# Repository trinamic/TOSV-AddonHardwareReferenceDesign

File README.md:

# TOSV-AddonHardwareReferenceDesign
Reference Design for the TOSV Pressure Sensor Addon Board

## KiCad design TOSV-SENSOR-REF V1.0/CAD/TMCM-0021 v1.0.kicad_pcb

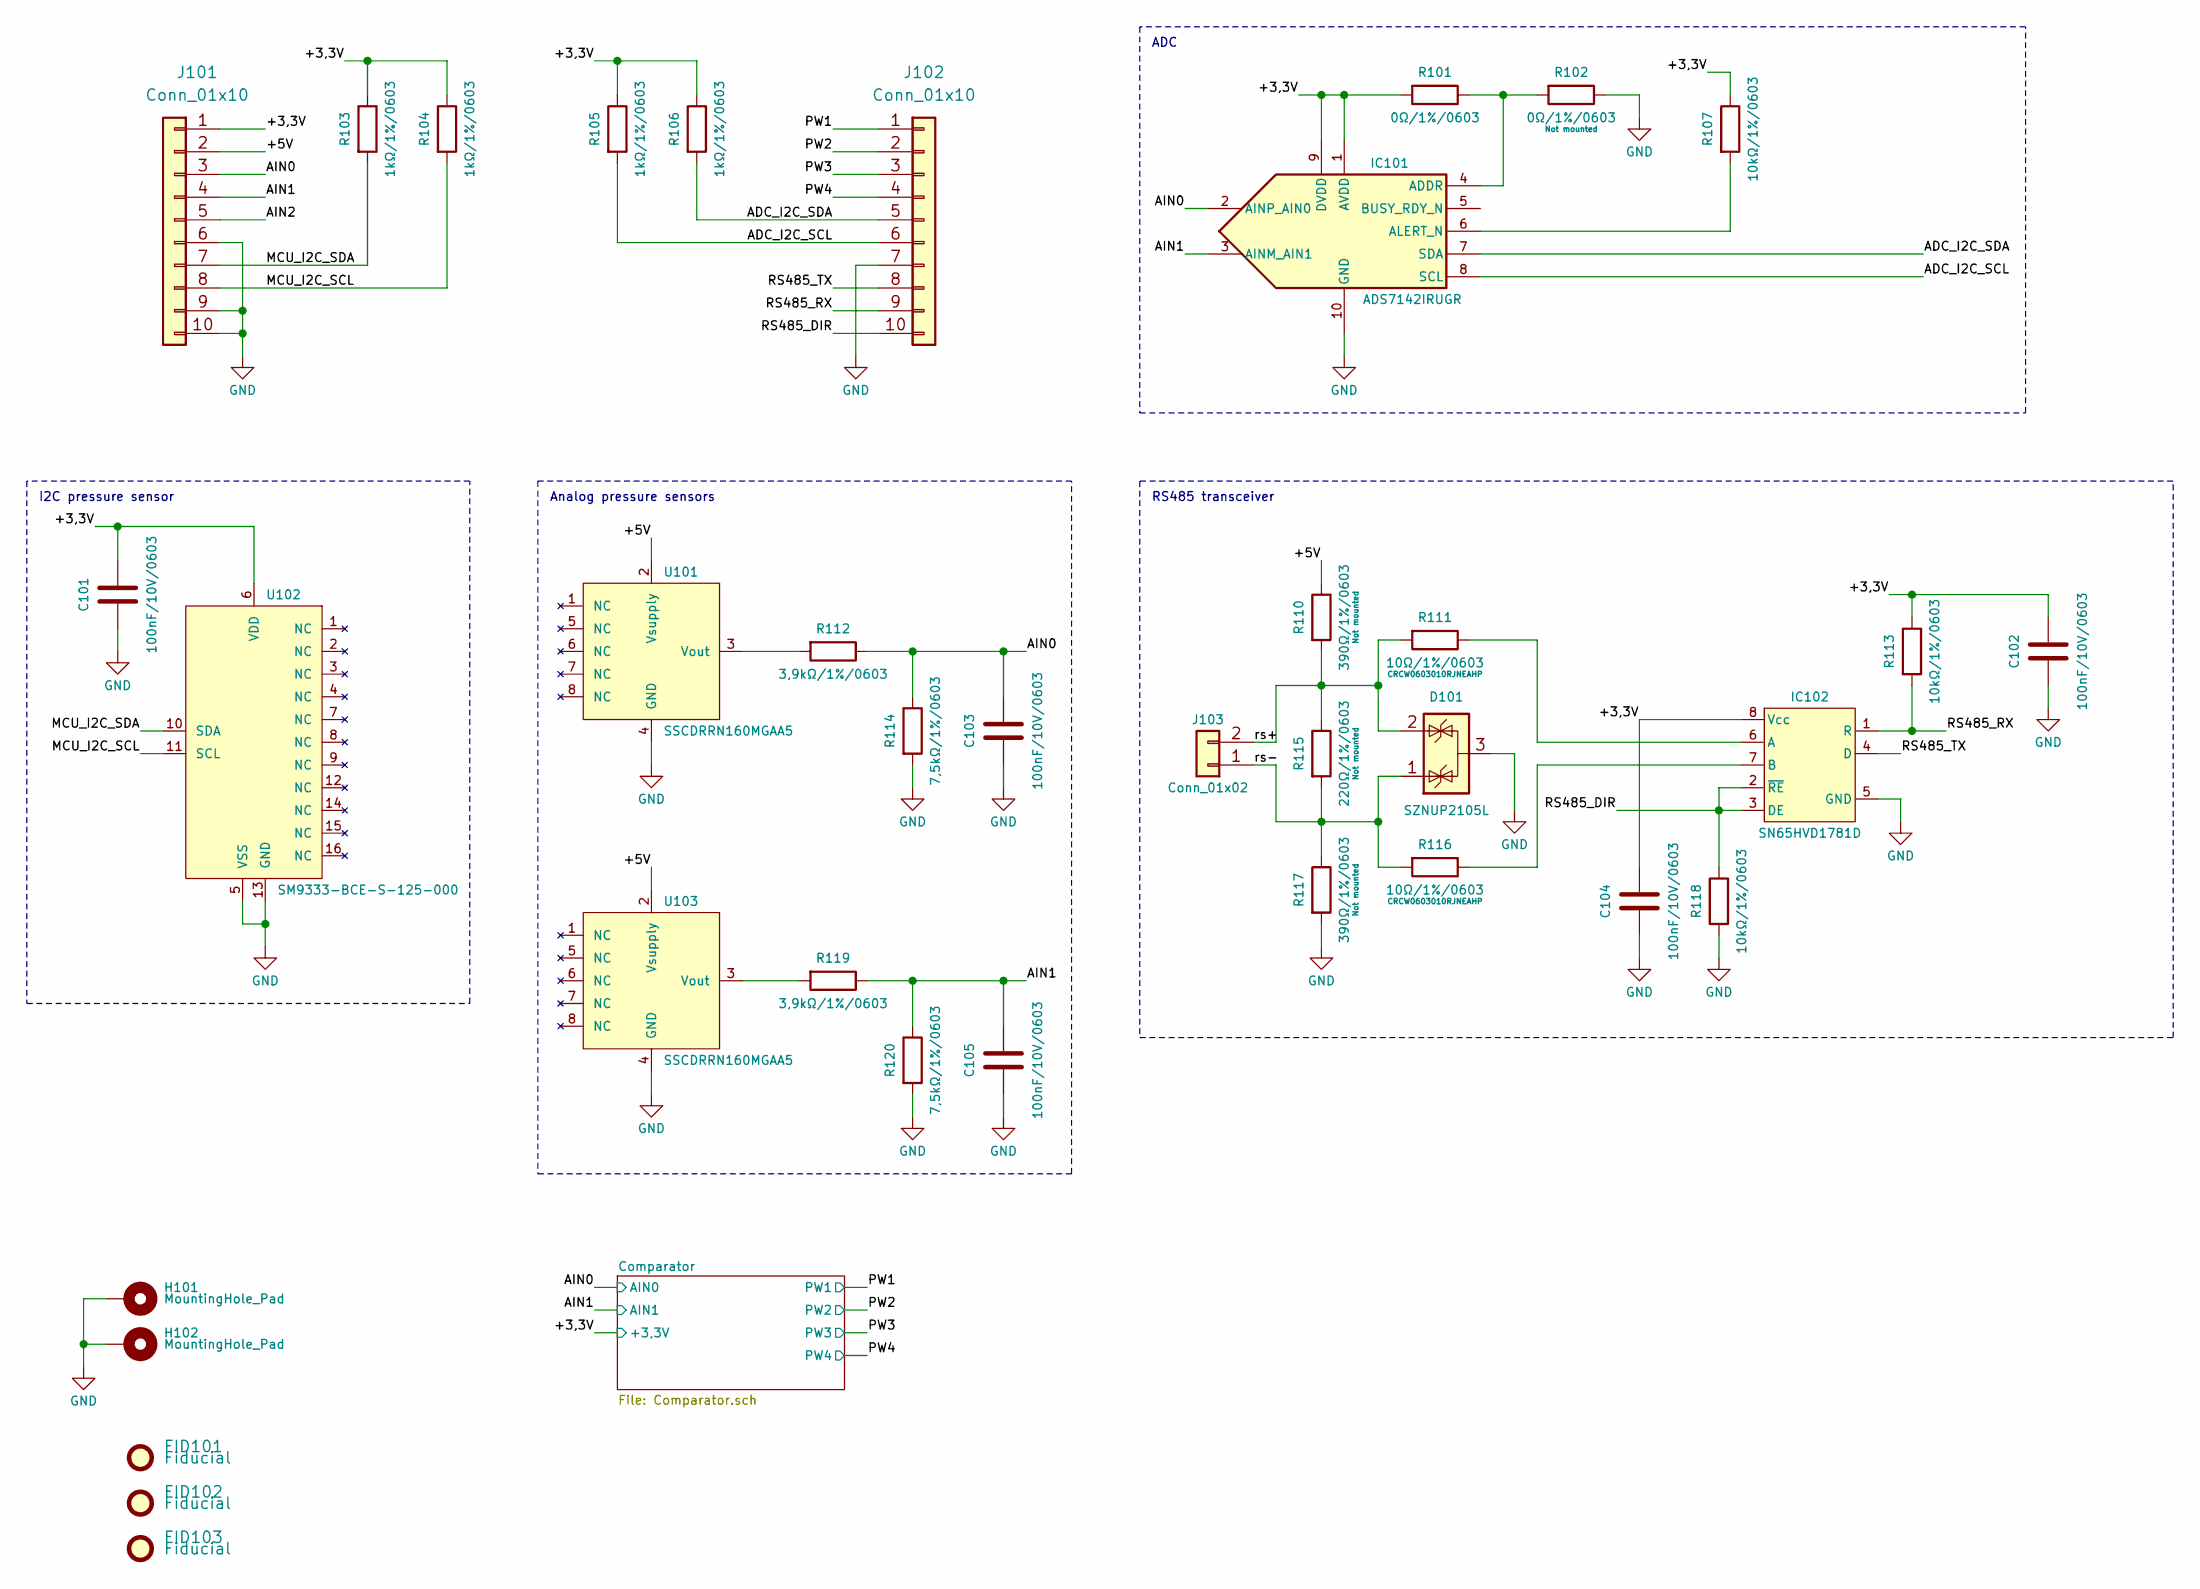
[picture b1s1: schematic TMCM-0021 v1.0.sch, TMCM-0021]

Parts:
C101, C102, C103, C104, C105: 100nF/10V/0603; C_0603_1608Metric
D101: SZNUP2105L; SOT-23
FID101, FID102, FID103: Fiducial; Fiducial_1mm_Mask2mm
H101, H102: MountingHole_Pad; MountingHole_3.2mm_M3_Pad
IC101: ADS7142IRUGR
IC102: SN65HVD1781D; SN65HVD1781DR
J101, J102: Conn_01x10; PinSocket_1x10_P2.54mm_Vertical
J103: Conn_01x02; PinHeader_1x02_P2.54mm_Vertical
R101, R102: 0Ω/1%/0603; R_0603_1608Metric
R103, R104, R105, R106: 1kΩ/1%/0603; R_0603_1608Metric
R107, R113, R118: 10kΩ/1%/0603; R_0603_1608Metric
R110, R117: 390Ω/1%/0603; R_0603_1608Metric
R111, R116: 10Ω/1%/0603; R_0603_1608Metric
R112, R119: 3,9kΩ/1%/0603; R_0603_1608Metric
R114, R120: 7,5kΩ/1%/0603; R_0603_1608Metric
R115: 220Ω/1%/0603; R_0603_1608Metric
U101, U103: SSCDRRN160MGAA5; DIP-8_W13.08mm
U102: SM9333-BCE-S-125-000; SOIC-16W_7.5x10.3mm_P1.27mm

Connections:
/+3,3V: C101.1, C102.1, C104.1, IC101.1 (AVDD), IC101.9 (DVDD), IC102.8 (Vcc), J101.1, R101.2, R103.1, R104.1, R105.1, R106.1, R107.1, R113.1, U102.6 (VDD); also elsewhere on the board
/+5V: J101.2, R110.1, U101.2 (Vsupply), U103.2 (Vsupply)
/ADC_I2C_SCL: IC101.8 (SCL), J102.6, R105.2
/ADC_I2C_SDA: IC101.7 (SDA), J102.5, R106.2
/AIN0: C103.1, IC101.2 (AINP_AIN0), J101.3, R112.1, R114.1; also elsewhere on the board
/AIN1: C105.1, IC101.3 (AINM_AIN1), J101.4, R119.1, R120.1; also elsewhere on the board
/MCU_I2C_SCL: J101.8, R104.2, U102.11 (SCL)
/MCU_I2C_SDA: J101.7, R103.2, U102.10 (SDA)
/PW1: J102.1; also elsewhere on the board
/PW2: J102.2; also elsewhere on the board
/PW3: J102.3; also elsewhere on the board
/PW4: J102.4; also elsewhere on the board
/RS485_DIR: IC102.2 (~RE), IC102.3 (DE), J102.10, R118.1
/RS485_RX: IC102.1 (R), J102.9, R113.2
/RS485_TX: IC102.4 (D), J102.8
/rs+: D101.2 (K), J103.2, R110.2, R111.2, R115.1
/rs-: D101.1 (K), J103.1, R115.2, R116.2, R117.1
GND: C101.2, C102.2, C103.2, C104.2, C105.2, D101.3 (A), H101.1, H102.1, IC101.10 (GND), IC102.5 (GND), J101.6, J101.9, J101.10, J102.7, R102.1, R114.2, R117.2, R118.2, R120.2, U101.4 (GND), U102.5 (VSS), U102.13 (GND), U103.4 (GND); also elsewhere on the board
unnamed: IC101.4 (ADDR), R101.1, R102.2
unnamed: IC101.6 (ALERT_N), R107.2
unnamed: IC102.6 (A), R111.1
unnamed: IC102.7 (B), R116.1
unnamed: R112.2, U101.3 (Vout)
unnamed: R119.2, U103.3 (Vout)

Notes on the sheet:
Analog pressure sensors
I2C pressure sensor
ADC
RS485 transceiver

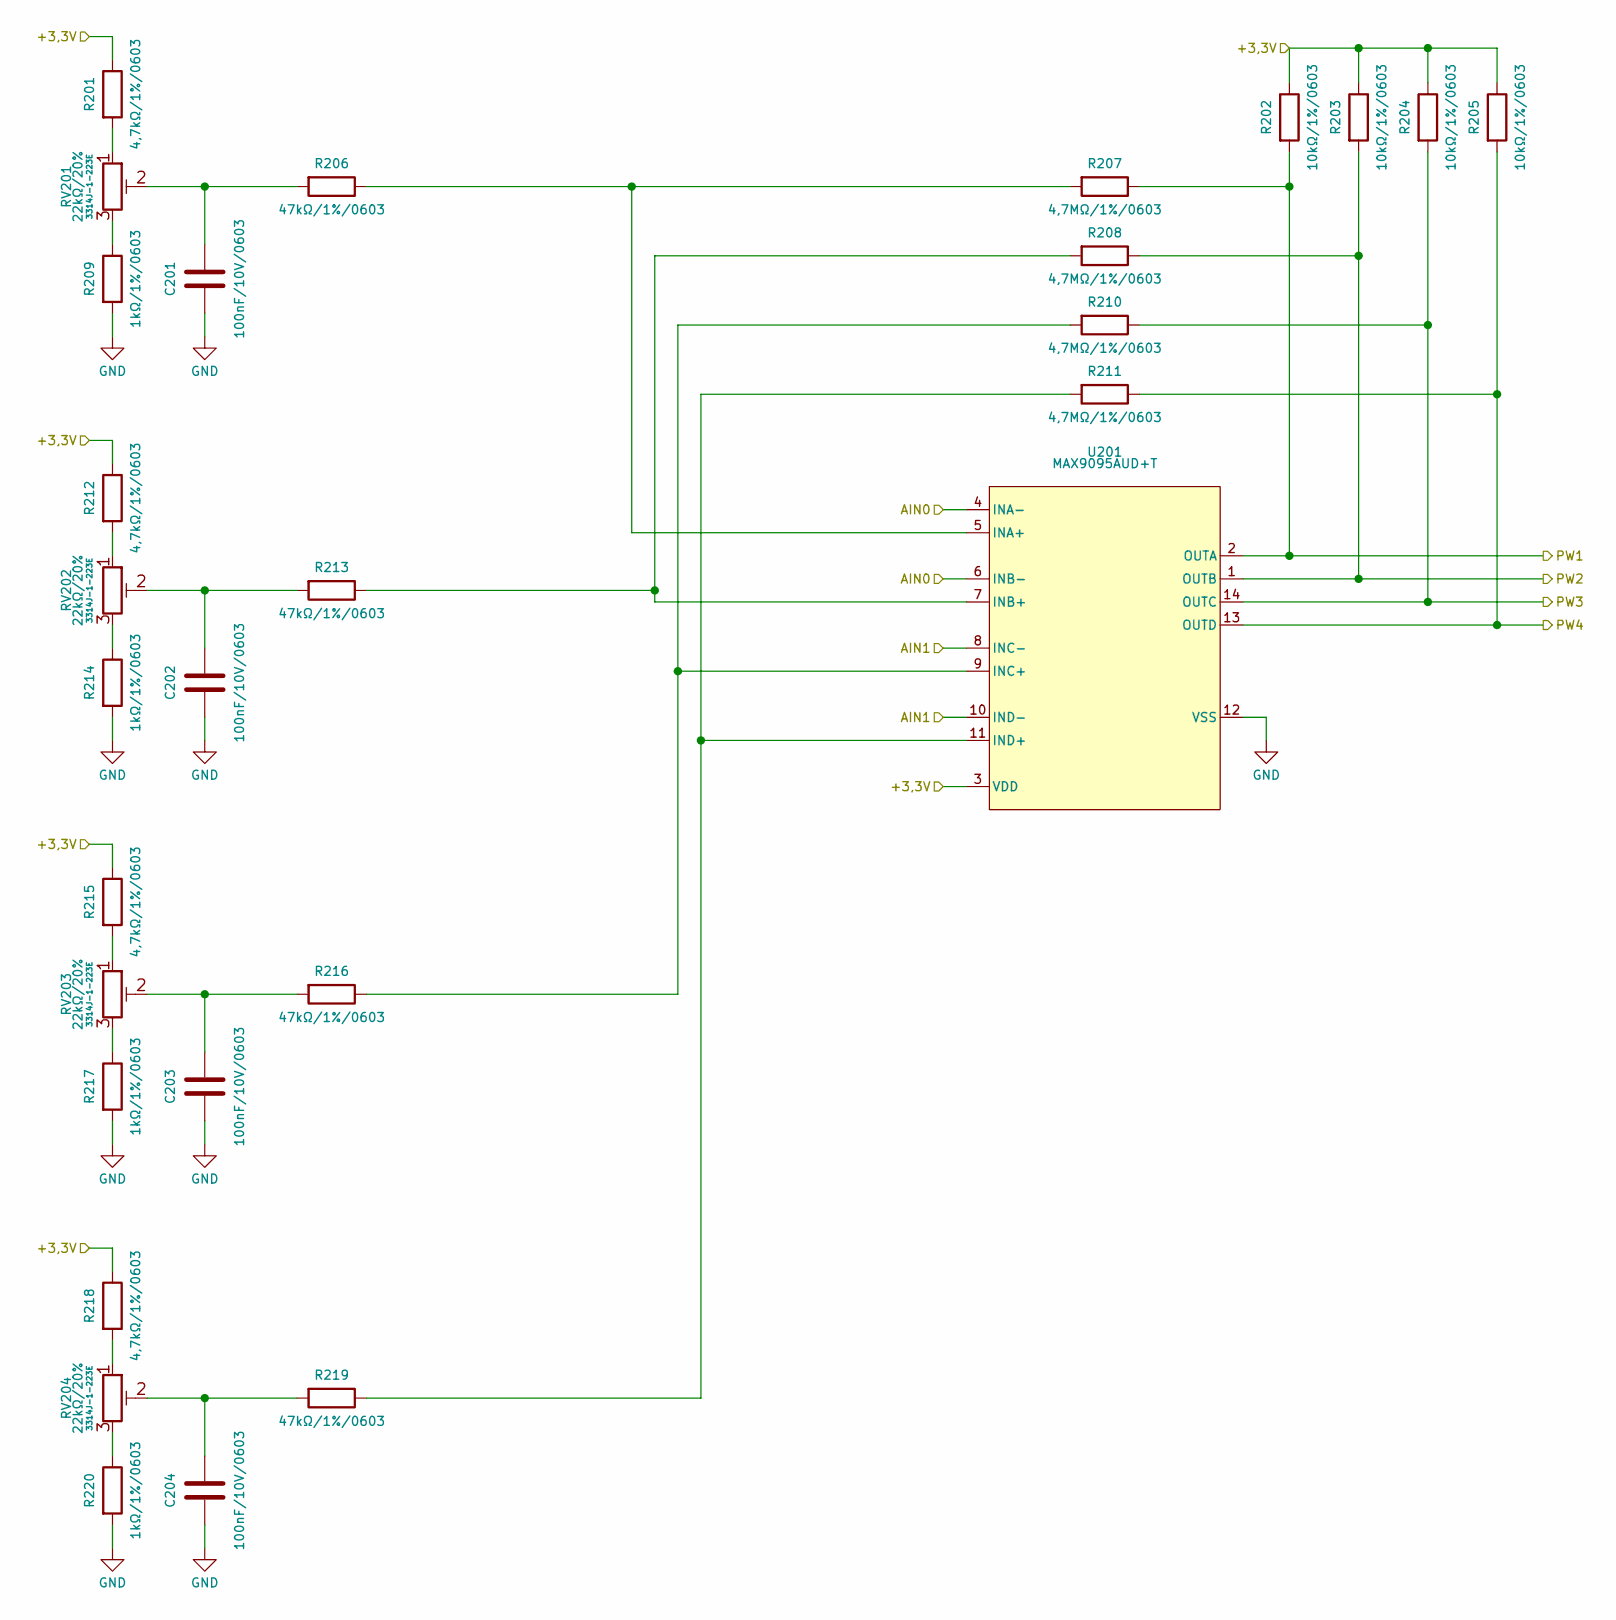
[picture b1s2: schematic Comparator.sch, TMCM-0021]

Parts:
C201, C202, C203, C204: 100nF/10V/0603; C_0603_1608Metric
R201, R212, R215, R218: 4,7kΩ/1%/0603; R_0603_1608Metric
R202, R203, R204, R205: 10kΩ/1%/0603; R_0603_1608Metric
R206, R213, R216, R219: 47kΩ/1%/0603; R_0603_1608Metric
R207, R208, R210, R211: 4,7MΩ/1%/0603; R_0603_1608Metric
R209, R214, R217, R220: 1kΩ/1%/0603; R_0603_1608Metric
RV201, RV202, RV203, RV204: 22kΩ/20%; Potentiometer_Bourns_3314J_Vertical
U201: MAX9095AUD+T; TSSOP-14_4.4x5mm_P0.65mm

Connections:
/+3,3V: R201.1, R202.1, R203.1, R204.1, R205.1, R212.1, R215.1, R218.1, U201.3 (VDD); also elsewhere on the board
/AIN0: U201.4 (INA-), U201.6 (INB-); also elsewhere on the board
/AIN1: U201.8 (INC-), U201.10 (IND-); also elsewhere on the board
/PW1: R202.2, R207.1, U201.2 (OUTA); also elsewhere on the board
/PW2: R203.2, R208.1, U201.1 (OUTB); also elsewhere on the board
/PW3: R204.2, R210.1, U201.14 (OUTC); also elsewhere on the board
/PW4: R205.2, R211.1, U201.13 (OUTD); also elsewhere on the board
GND: C201.2, C202.2, C203.2, C204.2, R209.2, R214.2, R217.2, R220.2, U201.12 (VSS); also elsewhere on the board
unnamed: C201.1, R206.2, RV201.2
unnamed: C202.1, R213.2, RV202.2
unnamed: C203.1, R216.2, RV203.2
unnamed: C204.1, R219.2, RV204.2
unnamed: R201.2, RV201.1
unnamed: R206.1, R207.2, U201.5 (INA+)
unnamed: R208.2, R213.1, U201.7 (INB+)
unnamed: R209.1, RV201.3
unnamed: R210.2, R216.1, U201.9 (INC+)
unnamed: R211.2, R219.1, U201.11 (IND+)
unnamed: R212.2, RV202.1
unnamed: R214.1, RV202.3
unnamed: R215.2, RV203.1
unnamed: R217.1, RV203.3
unnamed: R218.2, RV204.1
unnamed: R220.1, RV204.3

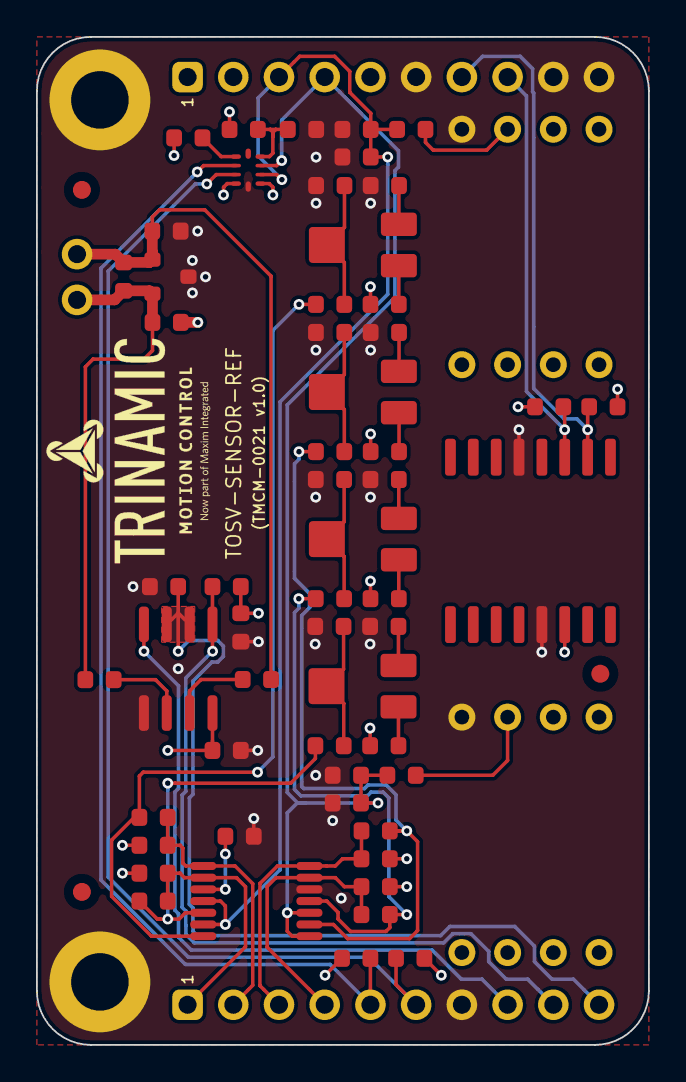
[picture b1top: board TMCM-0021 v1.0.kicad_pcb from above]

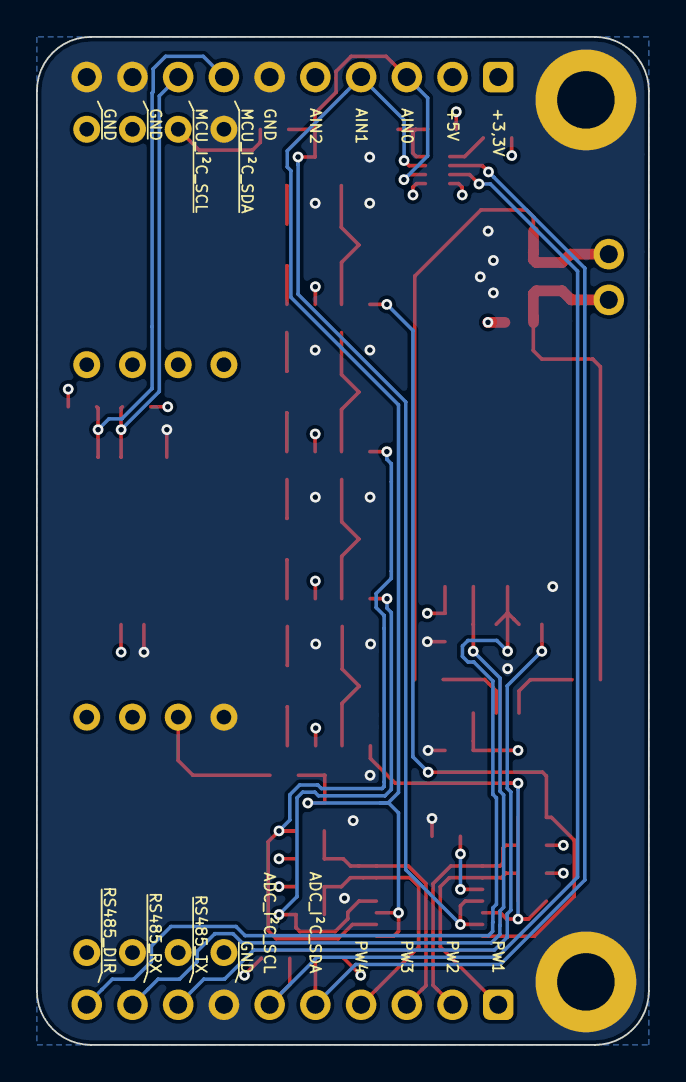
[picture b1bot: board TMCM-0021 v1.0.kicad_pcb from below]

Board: 4 copper layers, 34.0 x 56.0 mm, 66 parts (2 on the bottom side), 40 nets.

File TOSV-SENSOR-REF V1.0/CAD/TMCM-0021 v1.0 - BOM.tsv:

"Source:","C:\Users\Kurs\Work\TMCM-0021 v1.0\CAD\TMCM-0021 v1.0.sch"
"Date:","02.06.2020 14:54:51"
"Tool:","Eeschema (5.1.6)-1"
"Generator:","C:\Program Files\KiCad\bin\scripting\plugins/bom_csv_grouped_by_value_with_fp.py"
"Component Count:","66"
"Qnty","Ref","Value","Footprint","Info"
"9","C101, C102, C103, C104, C105, C201, C202, C203, C204, ","100nF/10V/0603","Capacitor_SMD:C_0603_1608Metric",""
"1","D101, ","SZNUP2105L","Package_TO_SOT_SMD:SOT-23",""
"3","FID101, FID102, FID103, ","Fiducial","Fiducial:Fiducial_1mm_Mask2mm",""
"2","H101, H102, ","MountingHole_Pad","MountingHole:MountingHole_3.2mm_M3_Pad",""
"1","IC101, ","ADS7142IRUGR","KiCad library:ADS7142IRUGR",""
"1","IC102, ","SN65HVD1781D","SN65HVD1781DR:SN65HVD1781DR",""
"2","J101, J102, ","Conn_01x10","Connector_PinSocket_2.54mm:PinSocket_1x10_P2.54mm_Vertical",""
"1","J103, ","Conn_01x02","Connector_PinHeader_2.54mm:PinHeader_1x02_P2.54mm_Vertical",""
"1","R101, ","0Ω/1%/0603","Resistor_SMD:R_0603_1608Metric",""
"1","R102, ","0Ω/1%/0603","Resistor_SMD:R_0603_1608Metric","Not mounted"
"8","R103, R104, R105, R106, R209, R214, R217, R220, ","1kΩ/1%/0603","Resistor_SMD:R_0603_1608Metric",""
"7","R107, R113, R118, R202, R203, R204, R205, ","10kΩ/1%/0603","Resistor_SMD:R_0603_1608Metric",""
"2","R110, R117, ","390Ω/1%/0603","Resistor_SMD:R_0603_1608Metric","Not mounted"
"2","R111, R116, ","10Ω/1%/0603","Resistor_SMD:R_0603_1608Metric","CRCW0603010RJNEAHP"
"2","R112, R119, ","3,9kΩ/1%/0603","Resistor_SMD:R_0603_1608Metric",""
"2","R114, R120, ","7,5kΩ/1%/0603","Resistor_SMD:R_0603_1608Metric",""
"1","R115, ","220Ω/1%/0603","Resistor_SMD:R_0603_1608Metric","Not mounted"
"4","R201, R212, R215, R218, ","4,7kΩ/1%/0603","Resistor_SMD:R_0603_1608Metric",""
"4","R206, R213, R216, R219, ","47kΩ/1%/0603","Resistor_SMD:R_0603_1608Metric",""
"4","R207, R208, R210, R211, ","4,7MΩ/1%/0603","Resistor_SMD:R_0603_1608Metric",""
"4","RV201, RV202, RV203, RV204, ","22kΩ/20%","Potentiometer_SMD:Potentiometer_Bourns_3314J_Vertical","3314J-1-223E"
"2","U101, U103, ","SSCDRRN160MGAA5","Package_DIP:DIP-8_W13.08mm",""
"1","U102, ","SM9333-BCE-S-125-000","Package_SO:SOIC-16W_7.5x10.3mm_P1.27mm",""
"1","U201, ","MAX9095AUD+T","Package_SO:TSSOP-14_4.4x5mm_P0.65mm",""

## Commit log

2020-06-11 First V1.0 Commit of the TOSV Pressure Sensor Reference Design
2020-06-11 3D file added and rendering update
    3D file in .step format and windows 3D viewer format.
2020-06-19 Silkscree Update
2020-06-19 Silkcreeen Update
2020-06-19 Silkscreen Top Update

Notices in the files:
parts and their libraries:
Copyright 2016 Accelerated Designs. All rights reserved.
